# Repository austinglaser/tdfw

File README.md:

# TDFW

An autonomous air-hockey table

# MDS

The Mallet Drive System ("MDS") is the low-level subsystem which controls the
table's mallet

## Interface

### Commands

Mnemonic              | Syntax                            
----------------------|-----------------------------------
Set pa**r**ameters    | `MR[X,Y]:<P>,<I>,<D>,<S>(,)\n`
Set **l**ocation      | `ML:<X>,<Y>(,)\n`
**S**tart             | `MS\n`
Sto**p**              | `MP\n`
**C**alibrate         | `MC\n`
Calibration **d**one  | `MD\n`

### Responses

Mnemonic                    | Syntax                            
----------------------------|-----------------------------------
MDS **o**n                  | `MO\n`
Command **a**cknowledged    | `MA\n`
**E**rror                   | `ME:<"error string">\n`
Calibration l**i**mits      | `MI:<Xmin>,<Xmax>,<Ymin>,<Ymax>\n`

### Syntax Reference

Syntax        |   Explanation
--------------|--------------------------------------------------------
`(c)`         | 'c' is optional, and does not affect syntax
`[c1,...,cn]` | one of 'c1' to 'cn' is required
`<n>`         | floating-point representation of 'n' is required
`<"string">`  | a string (perhaps including spaces) is required. Does not include quotation marks

All other characters are required verbatim

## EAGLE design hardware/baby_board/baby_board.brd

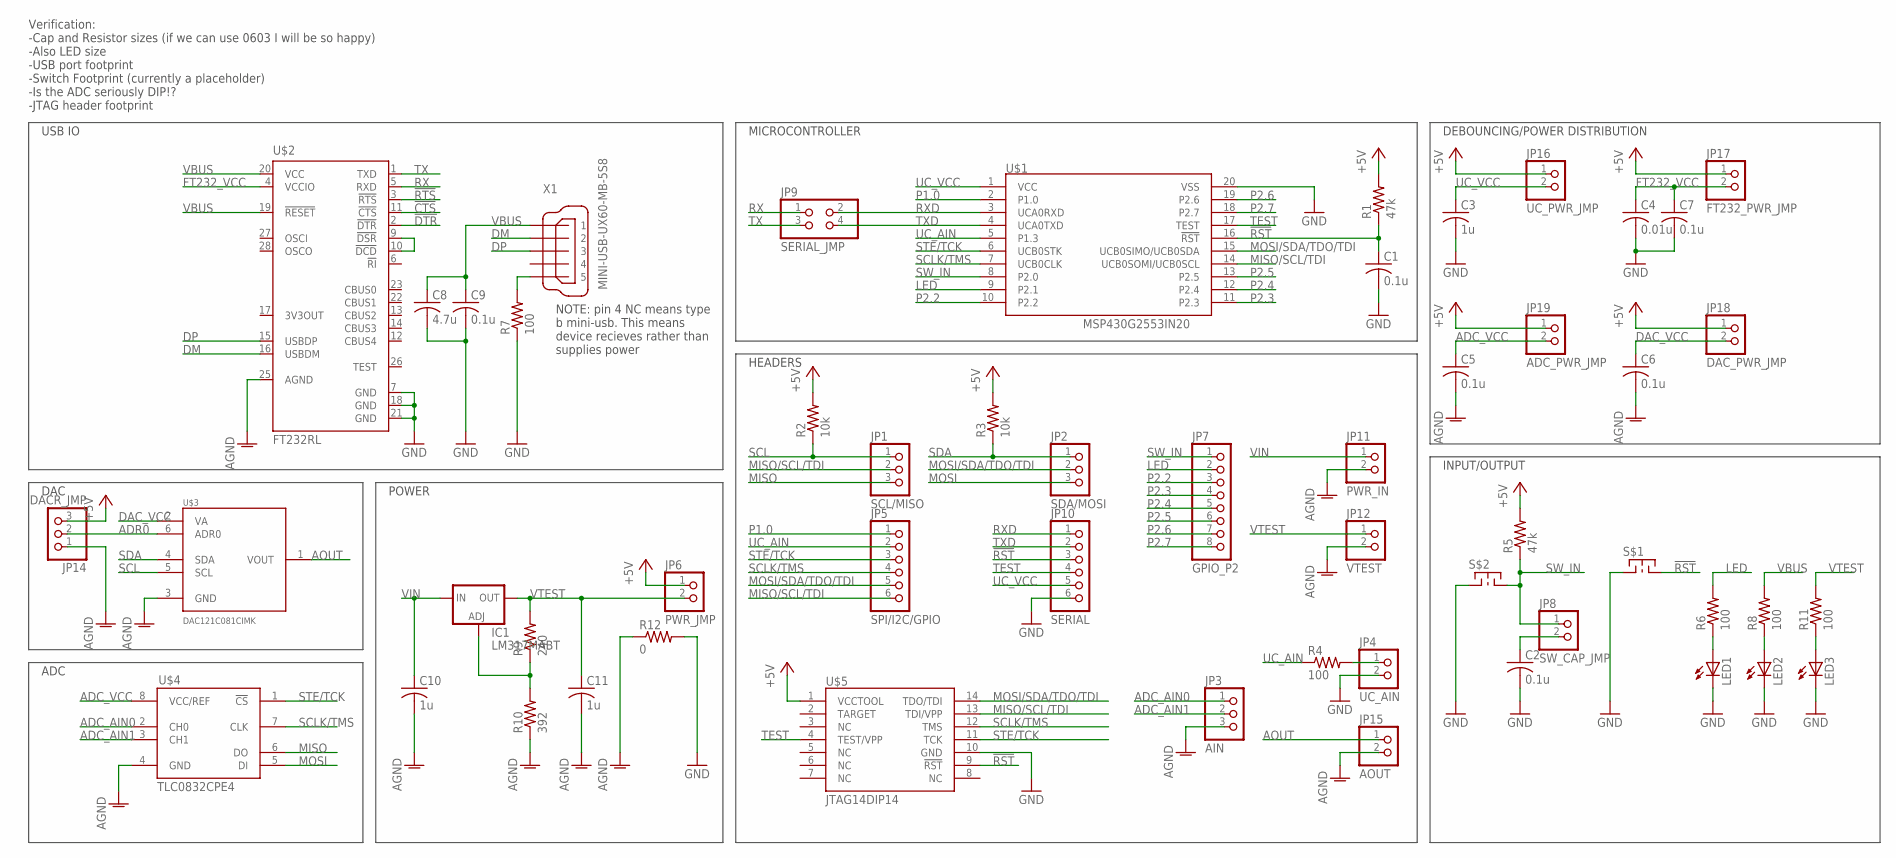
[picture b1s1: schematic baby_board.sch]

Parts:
C1, C2, C5, C6, C7, C9: 0.1u; C0603
C3, C10, C11: 1u; C0603
C4: 0.01u; C0603
C8: 4.7u; C0603
IC1: LM317MABT; TO220L1
JP1: SCL/MISO; 1X03
JP2: SDA/MOSI; 1X03
JP3: AIN; 1X03
JP4: UC_AIN; 1X02
JP5: SPI/I2C/GPIO; 1X06
JP6: PWR_JMP; 1X02
JP7: GPIO_P2; 1X08
JP8: SW_CAP_JMP; 1X02
JP9: SERIAL_JMP; 2X02
JP10: SERIAL; 1X06
JP11: PWR_IN; 1X02
JP12: VTEST; 1X02
JP14: DACR_JMP; 1X03
JP15: AOUT; 1X02
JP16: UC_PWR_JMP; 1X02
JP17: FT232_PWR_JMP; 1X02
JP18: DAC_PWR_JMP; 1X02
JP19: ADC_PWR_JMP; 1X02
LED1, LED2, LED3: LEDCHIP-LED0805; CHIP-LED0805
R1, R5: 47k; R0603
R2, R3: 10k; R0603
R4, R6, R7, R8, R11: 100; R0603
R9: 240; R0603
R10: 392; R0603
R12: 0; R0603
S$1, S$2: SWITCH_MOM_2_TEST; TEST
U$1: MSP430G2553IN20; 20-PDIP
U$2: FT232RL; SSOP28
U$3: DAC121C081CIMK; SOT-6
U$4: TLC0832CPE4; DIL08
U$5: JTAG14DIP14; DIL14
X1: MINI-USB-UX60-MB-5S8; UX60-MB-5S8

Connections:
!CTS: U$2.11 (!CTS)
!DTR: U$2.2 (!DTR)
!RST: C1.1, JP10.3, R1.1, S$1.2, U$1.16 (!RST), U$5.9 (!RST)
!RTS: U$2.3 (!RTS)
+5V: JP6.1, JP14.3, JP16.1, JP17.1, JP18.1, JP19.1, R1.2, R2.2, R3.2, R5.2, U$5.1 (VCCTOOL)
ADC_AIN0: JP3.1, U$4.2 (CH0)
ADC_AIN1: JP3.2, U$4.3 (CH1)
ADC_VCC: C5.1, JP19.2, U$4.8 (VCC/REF)
ADR0: JP14.2, U$3.6 (ADR0)
AGND: C5.2, C6.2, C10.2, C11.2, JP3.3, JP11.2, JP12.2, JP14.1, JP15.2, R10.1, R12.1, U$2.25 (AGND), U$3.3 (GND), U$4.4 (GND)
AOUT: JP15.1, U$3.1 (VOUT)
DAC_VCC: C6.1, JP18.2, U$3.2 (VA)
DM: U$2.16 (USBDM), X1.2
DP: U$2.15 (USBDP), X1.3
FT232_VCC: C4.1, C7.1, JP17.2, U$2.4 (VCCIO)
GND: C1.2, C2.2, C3.2, C4.2, C7.2, C8.2, C9.2, JP4.2, JP10.6, LED1.C, LED2.C, LED3.C, R7.1, R12.2, S$1.1, S$2.1, U$1.20 (VSS), U$2.7 (GND), U$2.18 (GND), U$2.21 (GND), U$5.10 (GND)
LED: JP7.2, R6.2, U$1.9 (P2.1)
MISO: JP1.3, U$4.6 (DO)
MISO/SCL/TDI: JP1.2, JP5.6, U$1.14 (UCB0SOMI/UCB0SCL), U$5.13 (TDI/VPP)
MOSI: JP2.3, U$4.5 (DI)
MOSI/SDA/TDO/TDI: JP2.2, JP5.5, U$1.15 (UCB0SIMO/UCB0SDA), U$5.14 (TDO/TDI)
unnamed: JP4.1, R4.2
unnamed: C2.1, JP8.2
unnamed: LED1.A, R6.1
unnamed: U$2.9 (!DSR), U$2.10 (!DCD)
unnamed: R7.2, X1.5
unnamed: LED2.A, R8.1
unnamed: IC1.1 (ADJ), R9.1, R10.2
unnamed: LED3.A, R11.1
P1.0: JP5.1, U$1.2 (P1.0)
P2.2: JP7.3, U$1.10 (P2.2)
P2.3: JP7.4, U$1.11 (P2.3)
P2.4: JP7.5, U$1.12 (P2.4)
P2.5: JP7.6, U$1.13 (P2.5)
P2.6: JP7.7, U$1.19 (P2.6)
P2.7: JP7.8, U$1.18 (P2.7)
RX: JP9.1, U$2.5 (RXD)
RXD: JP9.2, JP10.1, U$1.3 (UCA0RXD)
SCL: JP1.1, R2.1, U$3.5 (SCL)
SCLK/TMS: JP5.4, U$1.7 (UCB0CLK), U$4.7 (CLK), U$5.12 (TMS)
SDA: JP2.1, R3.1, U$3.4 (SDA)
STE/TCK: JP5.3, U$1.6 (UCB0STK), U$4.1 (!CS), U$5.11 (TCK)
SW_IN: JP7.1, JP8.1, R5.1, S$2.2, U$1.8 (P2.0)
TEST: JP10.4, U$1.17 (TEST), U$5.4 (TEST/VPP)
TX: JP9.3, U$2.1 (TXD)
TXD: JP9.4, JP10.2, U$1.4 (UCA0TXD)
UC_AIN: JP5.2, R4.1, U$1.5 (P1.3)
UC_VCC: C3.1, JP10.5, JP16.2, U$1.1 (VCC)
VBUS: C8.1, C9.1, R8.2, U$2.19 (!RESET), U$2.20 (VCC), X1.1
VIN: C10.1, IC1.3 (IN), JP11.1
VTEST: C11.1, IC1.2 (OUT), JP6.2, JP12.1, R9.2, R11.2

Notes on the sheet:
MICROCONTROLLER
INPUT/OUTPUT
HEADERS
DEBOUNCING/POWER DISTRIBUTION
NOTE: pin 4 NC means type b mini-usb. This means device recieves rather than supplies power
USB IO
POWER
DAC
Verification: -Cap and Resistor sizes (if we can use 0603 I will be so happy) -Also LED size -USB port footprint -Switch Footprint (currently a placeholder) -Is the ADC seriously DIP\!? -JTAG header footprint
ADC

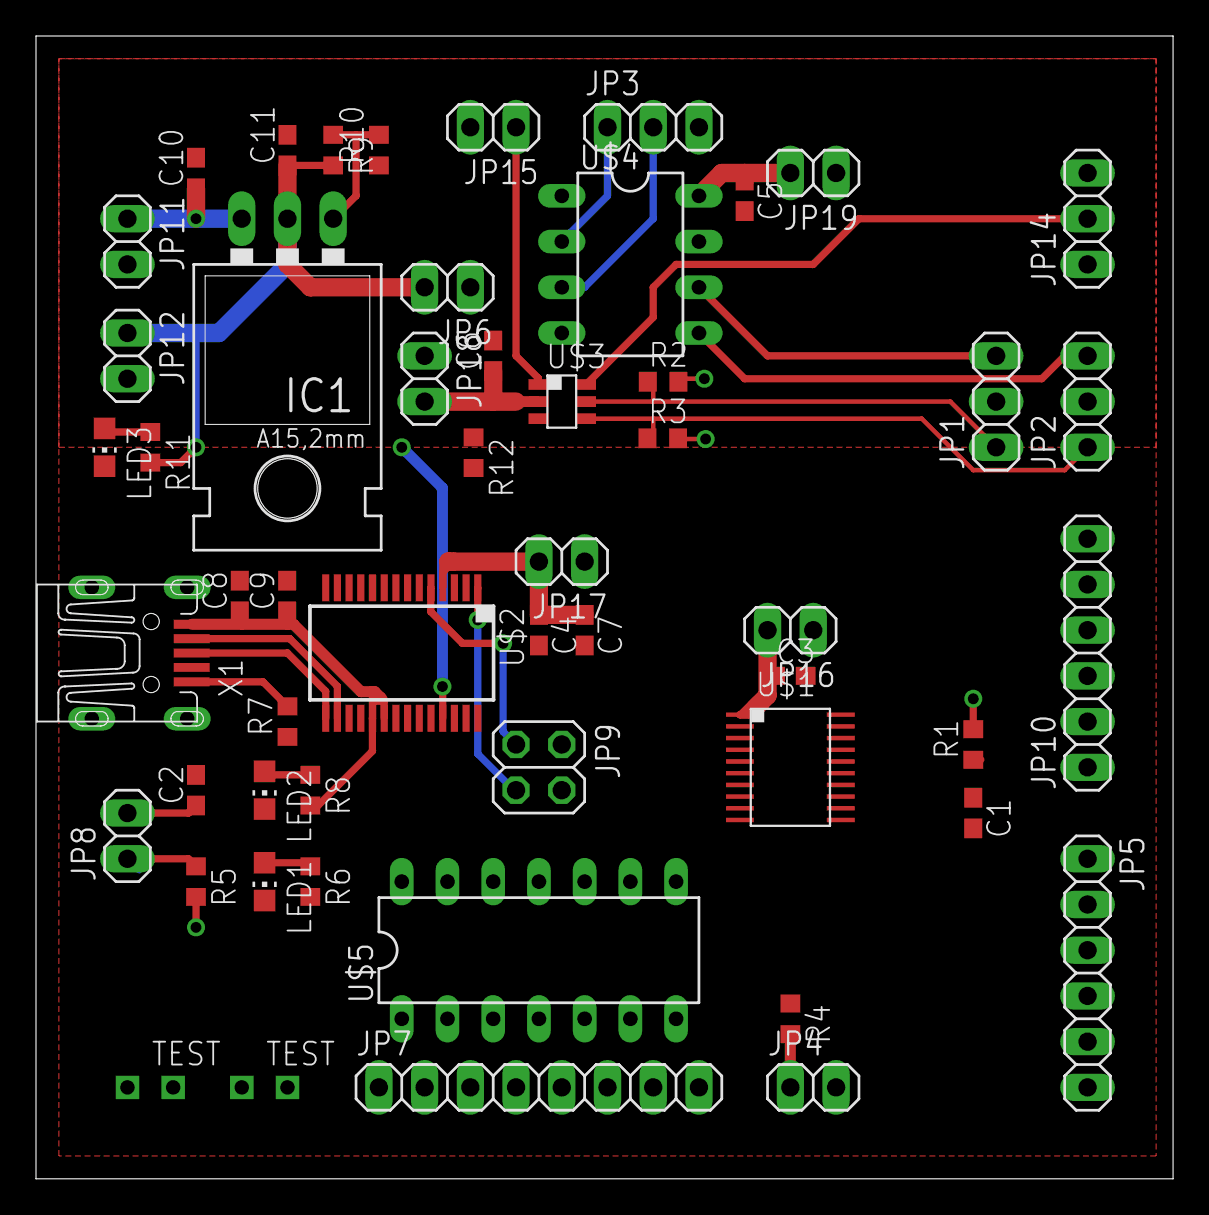
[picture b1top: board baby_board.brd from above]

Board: 2 copper layers, 63.2 x 63.5 mm, 53 parts (0 on the bottom side), 48 nets.

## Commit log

2014-09-09 add hardware block diagram to documentation
2014-09-09 add schematic and preliminary board layout
2014-11-13 add olinuxuino submodule
2015-02-05 added prelim vector prediction code
    uhyuhhhhhh
2015-02-05 make test.py executable
2015-02-05 make a main
2015-02-05 scratch
2015-02-05 add video files to gitignore
2015-02-05 get frames from camera
2015-02-05 rename folders
2015-02-10 adjust for real setup
2015-02-17 test of motor control
2015-02-17 add executable to gitignore
2015-02-17 working pin interrupt
2015-02-19 prelim version of motor control interface
2015-02-19 silence string warning
2015-02-19 prelim work on getting interrupts working on two pins
2015-02-19 bring in f303 motor driver code
2015-02-20 add files to gitignore
2015-02-20 remove accidentally committed files
2015-02-20 reorganize
2015-02-20 add documentation for f303
2015-02-20 starting point for motor driving code
2015-02-20 first pass mds interface
2015-02-20 added PID shit
2015-02-20 enable fpu
2015-02-20 halfway work on mds
2015-02-21 added correct PID also
2015-02-21 meow
2015-02-21 add prototypes for helper functions
2015-02-22 preliminary mds, without encoder interface code
2015-02-23 bring in std periph timer stuff
2015-02-23 bring in std periph rcc
2015-02-23 enable pwm in chibios
2015-02-23 remove assert_param() in std periph stuff
2015-02-23 first pass encoder interface
2015-02-23 working serial
2015-02-23 prelim counter working
2015-02-23 both encoders working!
2015-02-23 working pwm
2015-02-23 ignore eclipse files
2015-02-23 still not working
2015-02-24 take out pwm stuff temporarily, integration test 1
2015-02-24 change to timer 4 for pwm
2015-02-24 change chibios to remove isr in pwm code
2015-02-24 pwm working on tim1
2015-02-25 working pid!
2015-02-25 add tested pid constants (for unloaded pully)
2015-02-25 update some values and add error threshold
2015-02-26 update pid values
2015-02-26 add functionality to adjust saturation on the fly
2015-02-26 remove carriage returns
2015-02-26 some changes
2015-02-26 scoring
2015-02-26 remove extraneous header
2015-02-26 changes for integration test
2015-03-03 treat counter values as signed integers
2015-03-03 reduce movement interval
2015-03-03 clean up mds
2015-03-04 fix setpoint bug
2015-03-04 add test output
2015-03-04 add excel temp files to gitignore
2015-03-04 make chart!
2015-03-05 tests
2015-03-05 modify some values
2015-03-05 give y separate pid defaults and clean up code a little
2015-03-05 add motor_board submodule
2015-03-10 require y movement for conversion success
2015-03-12 working y direction
2015-03-17 add util functions
2015-03-17 first pass implementation of serial comms. Still buggy
2015-03-18 working serial interface
2015-03-18 increase PID loop frequency
2015-03-18 make some stuff in mds debug prints
2015-03-31 rename olimex scoring subfolder
2015-03-31 add meggers' ui stuff
2015-03-31 make python scripts executable
2015-03-31 added stds
2015-03-31 scoring working
2015-03-31 rename scoring
2015-03-31 new default loop constants
2015-03-31 make do comments
2015-03-31 meeeeoooowww
2015-03-31 make test.py executable because fuckboy fucked it up
2015-03-31 added fullscreen
2015-03-31 honk
2015-03-31 fix root error
2015-03-31 correct screen resolution
2015-03-31 add top-level run script
2015-03-31 make script find images wherever it's called from
2015-03-31 added shutdown function
2015-04-02 added button images
2015-04-02 big overhaul
2015-04-02 THIS STUPID IMAGE
2015-04-02 make do turn off
2015-04-02 fixmebuggyboy!
2015-04-02 add buffer flushing
2015-04-08 change calibration limit indicator
2015-04-08 add documentation for command set
2015-04-08 update command reference
2015-04-08 test with readme
2015-04-08 more readme experiments
2015-04-08 experaseraserment
2015-04-08 add emphasis
2015-04-08 add hierarchy
2015-04-08 add switch for echoing
2015-04-08 change start character
2015-04-08 whitespace fix
2015-04-08 Added all the MDS and vector prediction goodies!
2015-04-09 add olimex side of tcp
2015-04-09 add compy side of vector prediction
2015-04-09 got higher framerate working
2015-04-09 make main function
2015-04-09 make names actually fucking mean something
2015-04-09 strip out unnecessary shit and correct comments
2015-04-12 make listen threads exit properly
2015-04-12 change name
2015-04-12 not quite working yet
2015-04-12 fix sockets
2015-04-12 make ui exit gracefully in a some different corner cases
2015-04-12 add messages
2015-04-12 increase serial buffer
2015-04-13 adjust safety and dead zones
2015-04-13 more zone adjust
2015-04-13 tcp shite working
2015-04-13 final vector predicton
2015-04-13 add more tcp things
2015-04-13 more tcp things even
2015-04-13 make daemon actually work
2015-04-13 add tcp to vector prediction
2015-04-13 shamu
2015-04-13 add debug print
2015-04-14 It works.
2015-04-28 added audio folder
2015-04-28 added all audio wave files
2015-04-28 make threads die after a minute
2015-04-28 add play sound script
2015-04-28 move audio files
2015-04-28 indentation correction
2015-04-28 add play sound function
2015-04-28 remove extraneous print
2015-04-28 make more louderer
2015-04-28 more sounds and taunts
2015-04-29 FINAL REVISION
2017-04-14 Don't include ChibiOs tests
